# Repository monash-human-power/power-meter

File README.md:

# Cycling power meter final year project <!-- omit in toc -->
Oscar Varney and Jotham Gates, 2024

This is the code repository for a Final Year Project (FYP) to develop a crankset and power meter for Human Powered Vehicles (HPVs).

## Contents <!-- omit in toc -->
- [Getting started](#getting-started)
- [Schematic and PCB layout](#schematic-and-pcb-layout)
- [Code](#code)
  - [Libraries](#libraries)
  - [Tools for updating dates of changed files and versions](#tools-for-updating-dates-of-changed-files-and-versions)
    - [Git Hook for checking dates are correct before committing](#git-hook-for-checking-dates-are-correct-before-committing)
  - [Doxygen documentation](#doxygen-documentation)
- [Scripts and testing](#scripts-and-testing)

## Getting started
- See [here](./documents/getting_started_mqtt.md) for some instructions on getting the power meter to work with MQTT and WiFi.
- See [here](./configs/README.md) for information on configuring the power meter.
- See [here](./documents/mqtt_topics.md) for information on MQTT topics used when communicating using this protocol.
- If you are a member of MHP, then the Notion page for this project can be found [here](https://www.notion.so/monashhumanpower/Power-Pedals-Cranks-FYP-3e6eb409a05642b1ad961b32c2f40aa7).
- The reports submitted for the project are [here](https://github.com/monash-human-power/power-meter-docs/releases) (private repository).

## Schematic and PCB layout
The schematic and PCB layout were completed using [KiCAD 9](https://www.kicad.org/). The design files are in the [`power-meter-pcb`](./power-meter-pcb/) folder.

## Code
The firmware is written to use the Arduino environment of Platform IO and is located in the [`power-meter-code`](power-meter-code) directory.

### Libraries
Install the following libraries, either by using the Arduino library manager or going to their GitHub repository and cloning them.
- [ArduinoJson](https://arduinojson.org/) library for JSON encoding and decoding.
- [ICM42670P](https://github.com/tdk-invn-oss/motion.arduino.ICM42670P) library for communicating with the IMU.
- [BasicLinearAlgebra](https://github.com/tomstewart89/BasicLinearAlgebra/) library for matrix maths. This is also added as a submodule for testing the Kalman filter on a computer.
- [ArduinoBLE](https://github.com/arduino-libraries/ArduinoBLE) library for Bluetooth Low Energy (BLE) communications.
- [PubSubClient](https://pubsubclient.knolleary.net/) library for communicating using MQTT over WiFi.

### Tools for updating dates of changed files and versions
A bash script has been written to update the dates on all modified or staged files (not including untracked files). To perform this operation, run:
```bash
./tools/update_date.sh
```

Another script is included to update the version info on all files and definitions for the code. The files and elements updated include:
- Any `@version` tags in the code directory.
- The `VERSION` definition in [`defines.h`](./power-meter-code/defines.h).
- The Doxygen version number in [`Doxyfile`](./Doxyfile).

As an example:
```bash
./tools/update_version.sh 1.2.3
```

#### Git Hook for checking dates are correct before committing
> This needs to be modified to work with the platform IO structure.
Copy the [`pre-commit`](./tools/pre-commit) file into [`.git/hooks/pre-commit`](.git/hooks/pre-commit). This will check the date of code files and make sure they are up to date.

### Doxygen documentation
Documentation can be automatically generated using Doxygen by running `doxygen` from the root folder of the repository. You might need to install doxygen and graphviz first. The output will be placed in the [`docs`](docs) folder. GitHub actions may be set up later down the track to automatically generate and deploy to GitHub pages on commit- however that would require a public repository and documentation.

To generate a massive appendix for the report, run `./tools/generate_refman.sh`

The output file will be [`refman.pdf`](docs/latex/refman.pdf).

## Scripts and testing
Scripts for testing the board hardware and easing development of certain sections can be found in the [`scripts-testing`](./scripts-testing/) directory. This includes python scripts used to log data over MQTT and plot it.

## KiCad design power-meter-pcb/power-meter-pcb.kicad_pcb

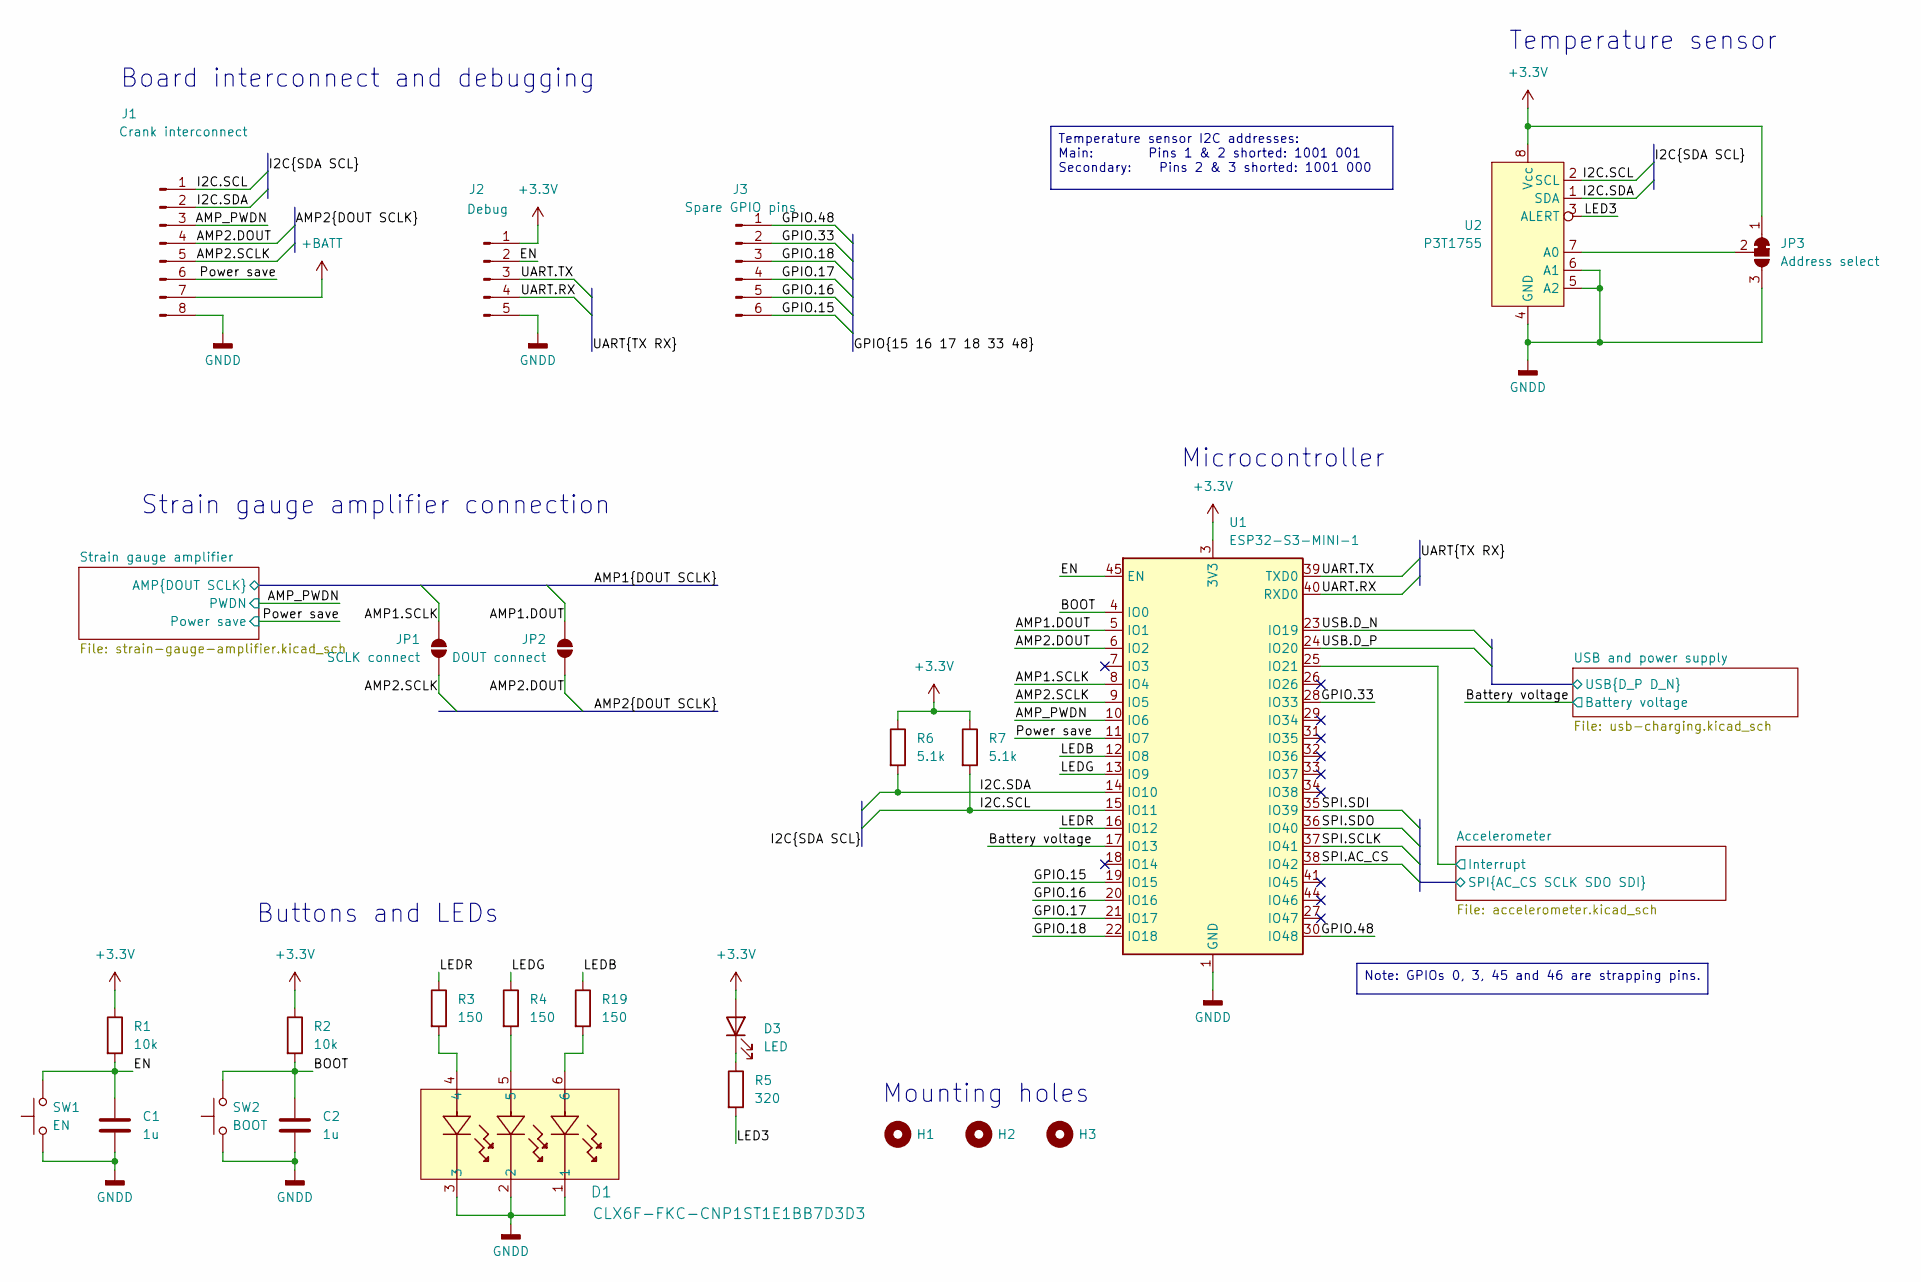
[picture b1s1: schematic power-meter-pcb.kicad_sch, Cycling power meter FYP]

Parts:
C1, C2: 1u; C_0603_1608Metric_Pad1.08x0.95mm_HandSolder
D1: CLX6F-FKC-CNP1ST1E1BB7D3D3; PLCC6_3.4X3.4_CRW-M
D3: LED; LED_0603_1608Metric_Pad1.05x0.95mm_HandSolder
H1, H2, H3: MountingHole; MountingHole_2.2mm_M2
J1: Crank interconnect; JST_PH_S8B-PH-K_1x08_P2.00mm_Horizontal
J2: Debug; PinHeader_1x05_P2.54mm_Vertical
J3: Spare GPIO pins; PinHeader_1x06_P2.00mm_Vertical
JP1: SCLK connect; SolderJumper-2_P1.3mm_Open_RoundedPad1.0x1.5mm
JP2: DOUT connect; SolderJumper-2_P1.3mm_Open_RoundedPad1.0x1.5mm
JP3: Address select; SolderJumper-3_P1.3mm_Open_RoundedPad1.0x1.5mm
R1, R2: 10k; R_0603_1608Metric_Pad0.98x0.95mm_HandSolder
R3, R4, R19: 150; R_0603_1608Metric_Pad0.98x0.95mm_HandSolder
R5: 320; R_0603_1608Metric_Pad0.98x0.95mm_HandSolder
R6, R7: 5.1k; R_0603_1608Metric_Pad0.98x0.95mm_HandSolder
SW1: EN; SW_Push_1P1T_NO_CK_KMR2
SW2: BOOT; SW_Push_1P1T_NO_CK_KMR2
U1: ESP32-S3-MINI-1; ESP32-S2-MINI-1
U2: P3T1755; TSSOP-8_3x3mm_P0.65mm

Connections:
+3.3V: D3.2 (A), J2.1, JP3.1 (A), R1.1, R2.1, R6.1, R7.1, U1.3 (3V3), U2.8 (Vcc); also elsewhere on the board
+BATT: J1.7; also elsewhere on the board
/AMP1.DOUT: JP2.2 (B), U1.5 (IO1); also elsewhere on the board
/AMP1.SCLK: JP1.2 (B), U1.8 (IO4); also elsewhere on the board
/AMP2.DOUT: J1.4, JP2.1 (A), U1.6 (IO2)
/AMP2.SCLK: J1.5, JP1.1 (A), U1.9 (IO5)
/AMP_PWDN: J1.3, U1.10 (IO6); also elsewhere on the board
/Accelerometer/Interrupt: U1.25 (IO21); also elsewhere on the board
/Accelerometer/SPI.AC_CS: U1.38 (IO42); also elsewhere on the board
/Accelerometer/SPI.SCLK: U1.37 (IO41); also elsewhere on the board
/Accelerometer/SPI.SDI: U1.35 (IO39); also elsewhere on the board
/Accelerometer/SPI.SDO: U1.36 (IO40); also elsewhere on the board
/BOOT: C2.2, R2.2, SW2.2, U1.4 (IO0)
/Battery voltage: U1.17 (IO13); also elsewhere on the board
/EN: C1.2, J2.2, R1.2, SW1.2, U1.45 (EN)
/GPIO.15: J3.6, U1.19 (IO15)
/GPIO.16: J3.5, U1.20 (IO16)
/GPIO.17: J3.4, U1.21 (IO17)
/GPIO.18: J3.3, U1.22 (IO18)
/GPIO.33: J3.2, U1.28 (IO33)
/GPIO.48: J3.1, U1.30 (IO48)
/I2C.SCL: J1.1, R7.2, U1.15 (IO11), U2.2 (SCL)
/I2C.SDA: J1.2, R6.2, U1.14 (IO10), U2.1 (SDA)
/LED3: R5.2, U2.3 (ALERT)
/LEDB: R19.1, U1.12 (IO8)
/LEDG: R4.1, U1.13 (IO9)
/LEDR: R3.1, U1.16 (IO12)
/Power save: J1.6, U1.11 (IO7); also elsewhere on the board
/UART.RX: J2.4, U1.40 (RXD0)
/UART.TX: J2.3, U1.39 (TXD0)
/USB and power supply/USB.D_N: U1.23 (IO19); also elsewhere on the board
/USB and power supply/USB.D_P: U1.24 (IO20); also elsewhere on the board
GNDD: C1.1, C2.1, D1.1, D1.2, D1.3, J1.8, J2.5, JP3.3 (B), SW1.1, SW2.1, U1.1 (GND), U1.2 (GND), U1.42 (GND), U1.43 (GND), U1.46 (GND), U1.47 (GND), U1.48 (GND), U1.49 (GND), U1.50 (GND), U1.51 (GND), U1.52 (GND), U1.53 (GND), U1.54 (GND), U1.55 (GND), U1.56 (GND), U1.57 (GND), U1.58 (GND), U1.59 (GND), U1.60 (GND), U1.61 (GND), U1.62 (GND), U1.63 (GND), U1.64 (GND), U1.65 (GND), U2.4 (GND), U2.5 (A2), U2.6 (A1); also elsewhere on the board
unnamed: D1.4, R3.2
unnamed: D1.5, R4.2
unnamed: D1.6, R19.2
unnamed: D3.1 (K), R5.1
unnamed: JP3.2 (C), U2.7 (A0)

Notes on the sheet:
Board interconnect and debugging
Buttons and LEDs
Strain gauge amplifier connection
Microcontroller
Mounting holes
Temperature sensor
Note: GPIOs 0, 3, 45 and 46 are strapping pins.
Temperature sensor I2C addresses: Main: Pins 1 & 2 shorted: 1001 001 Secondary: Pins 2 & 3 shorted: 1001 000

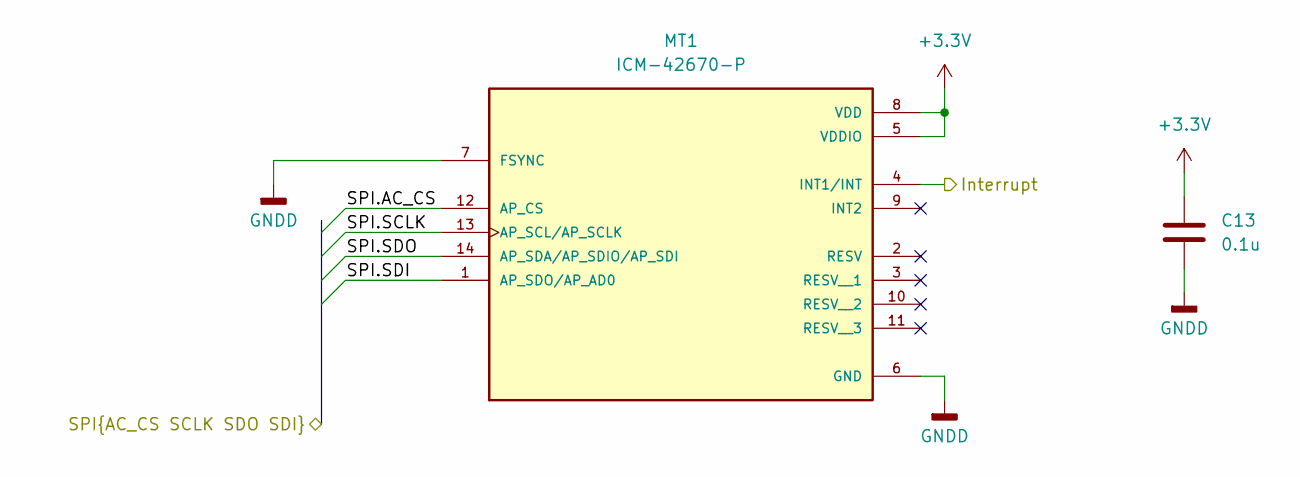
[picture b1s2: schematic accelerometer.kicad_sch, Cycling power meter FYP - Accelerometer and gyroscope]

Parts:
C13: 0.1u; C_0603_1608Metric_Pad1.08x0.95mm_HandSolder
MT1: ICM-42670-P; XDCR_ICM-42670-P; PARTREV 1.1

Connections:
+3.3V: C13.1, MT1.5 (VDDIO), MT1.8 (VDD); also elsewhere on the board
/Accelerometer/Interrupt: MT1.4 (INT1/INT); also elsewhere on the board
/Accelerometer/SPI.AC_CS: MT1.12 (AP_CS); also elsewhere on the board
/Accelerometer/SPI.SCLK: MT1.13 (AP_SCL/AP_SCLK); also elsewhere on the board
/Accelerometer/SPI.SDI: MT1.1 (AP_SDO/AP_AD0); also elsewhere on the board
/Accelerometer/SPI.SDO: MT1.14 (AP_SDA/AP_SDIO/AP_SDI); also elsewhere on the board
GNDD: C13.2, MT1.6 (GND), MT1.7 (FSYNC); also elsewhere on the board

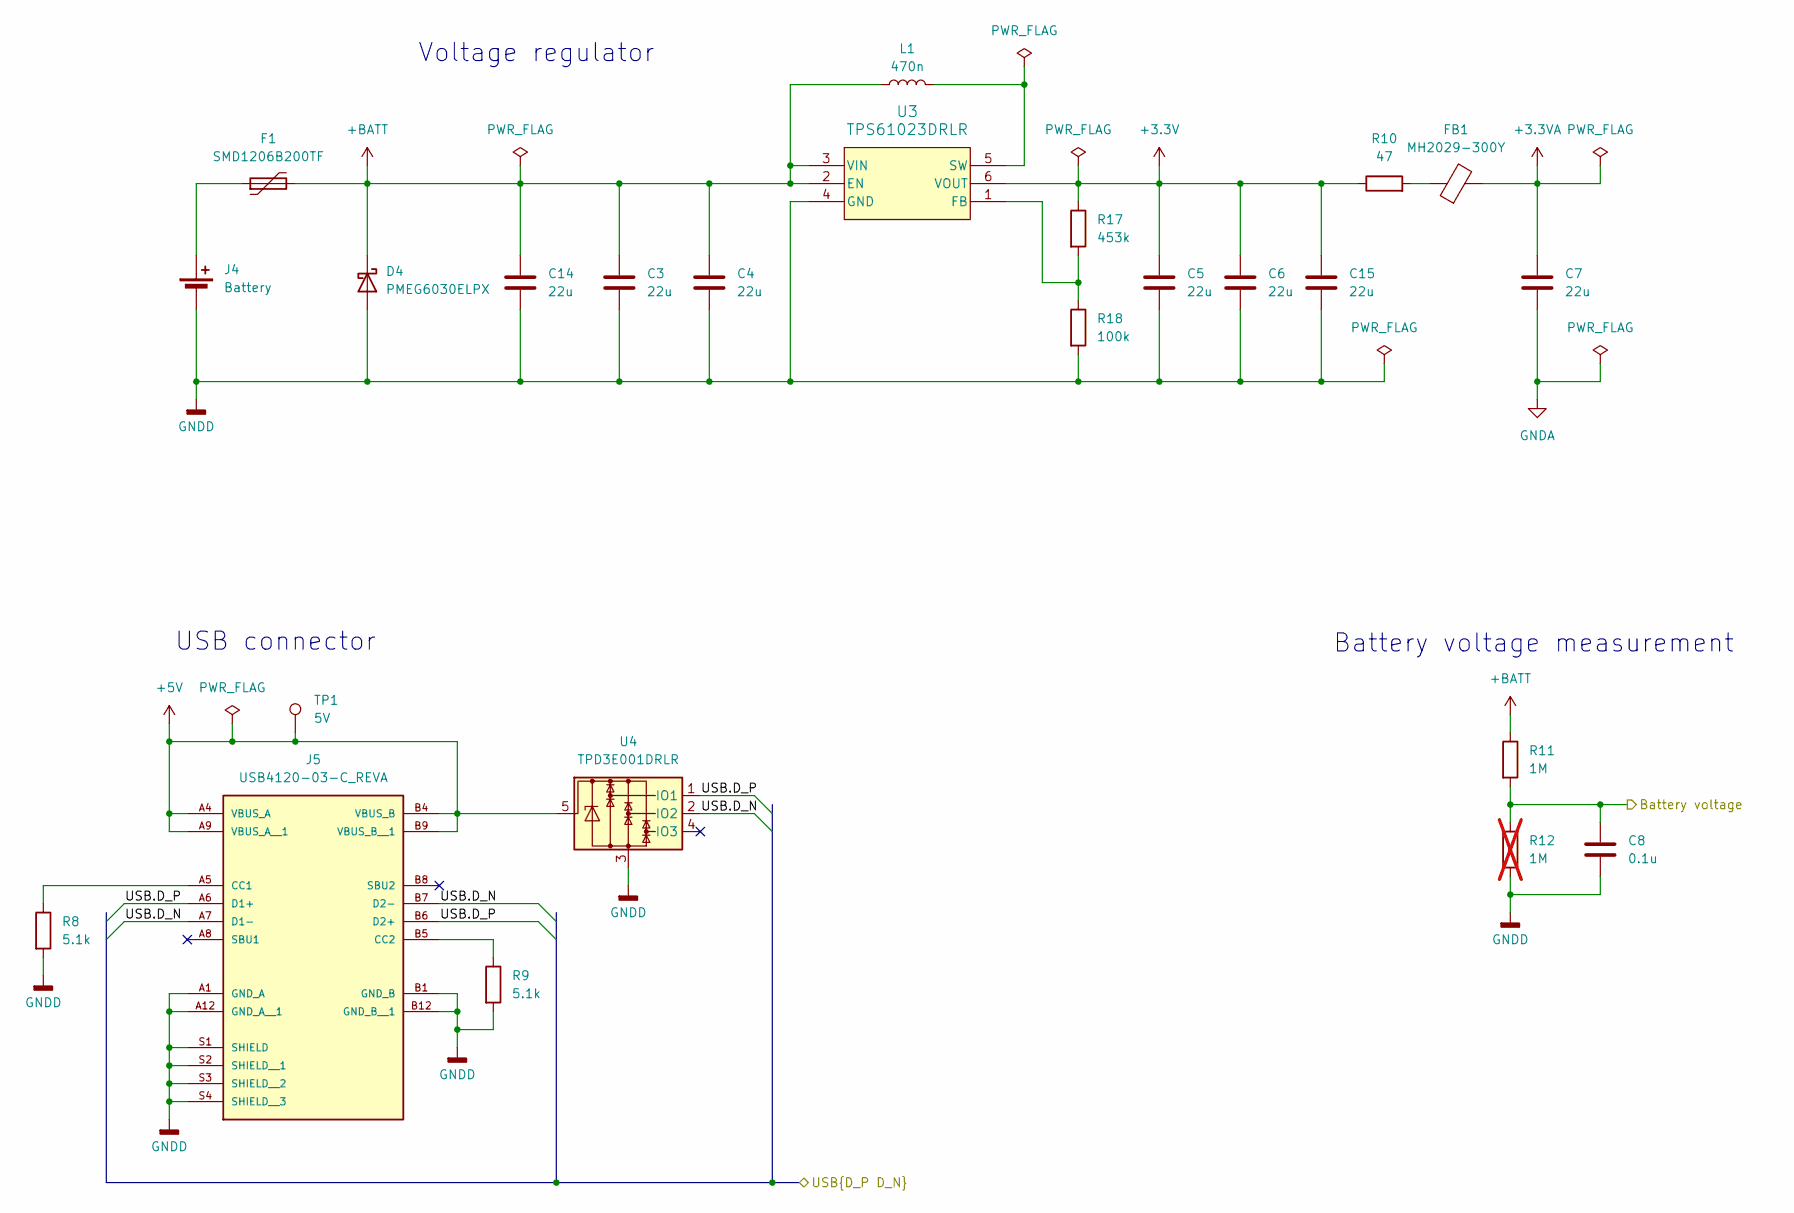
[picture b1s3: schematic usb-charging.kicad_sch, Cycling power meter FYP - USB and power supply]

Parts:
C3, C4, C5, C6, C7, C14, C15: 22u; C_0603_1608Metric_Pad1.08x0.95mm_HandSolder
C8: 0.1u; C_0603_1608Metric_Pad1.08x0.95mm_HandSolder
D4: PMEG6030ELPX; D_SOD-128
F1: SMD1206B200TF; Fuse_1206_3216Metric_Pad1.42x1.75mm_HandSolder
FB1: MH2029-300Y; L_0805_2012Metric
J4: Battery; JST_PH_S2B-PH-K_1x02_P2.00mm_Horizontal
J5: USB4120-03-C_REVA; GCT_USB4120-03-C_REVA; PARTREV A
L1: 470n; L_Vishay_IHLP-1212
R8, R9: 5.1k; R_0603_1608Metric_Pad0.98x0.95mm_HandSolder
R10: 47; R_0603_1608Metric_Pad0.98x0.95mm_HandSolder
R11: 1M; R_0603_1608Metric_Pad0.98x0.95mm_HandSolder
R12: 1M; R_0603_1608Metric_Pad0.98x0.95mm_HandSolder; not fitted
R17: 453k; R_0603_1608Metric_Pad0.98x0.95mm_HandSolder
R18: 100k; R_0603_1608Metric_Pad0.98x0.95mm_HandSolder
TP1: 5V; TestPoint_Pad_1.5x1.5mm
U3: TPS61023DRLR; DRL0006A
U4: TPD3E001DRLR; SOT-553

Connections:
+3.3V: C5.1, C6.1, C15.1, R10.1, R17.1, U3.6 (VOUT); also elsewhere on the board
+3.3VA: C7.1, FB1.2; also elsewhere on the board
+5V: J5.A4 (VBUS_A), J5.A9 (VBUS_A__1), J5.B4 (VBUS_B), J5.B9 (VBUS_B__1), TP1.1, U4.5
+BATT: C3.1, C4.1, C14.1, D4.1 (K), F1.2, L1.1, R11.1, U3.2 (EN), U3.3 (VIN); also elsewhere on the board
/Battery voltage: C8.1, R11.2, R12.1; also elsewhere on the board
/USB and power supply/USB.D_N: J5.A7 (D1-), J5.B7 (D2-), U4.2 (IO2); also elsewhere on the board
/USB and power supply/USB.D_P: J5.A6 (D1+), J5.B6 (D2+), U4.1 (IO1); also elsewhere on the board
GNDA: C7.2; also elsewhere on the board
GNDD: C3.2, C4.2, C5.2, C6.2, C8.2, C14.2, C15.2, D4.2 (A), J4.2 (-), J5.A1 (GND_A), J5.A12 (GND_A__1), J5.B1 (GND_B), J5.B12 (GND_B__1), J5.S1 (SHIELD), J5.S2 (SHIELD__1), J5.S3 (SHIELD__2), J5.S4 (SHIELD__3), R8.2, R9.2, R12.2, R18.2, U3.4 (GND), U4.3; also elsewhere on the board
unnamed: FB1.1, R10.2
unnamed: F1.1, J4.1 (+)
unnamed: J5.A5 (CC1), R8.1
unnamed: J5.B5 (CC2), R9.1
unnamed: R17.2, R18.1, U3.1 (FB)
unnamed: L1.2, U3.5 (SW)

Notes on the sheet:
Battery voltage measurement
USB connector
Voltage regulator

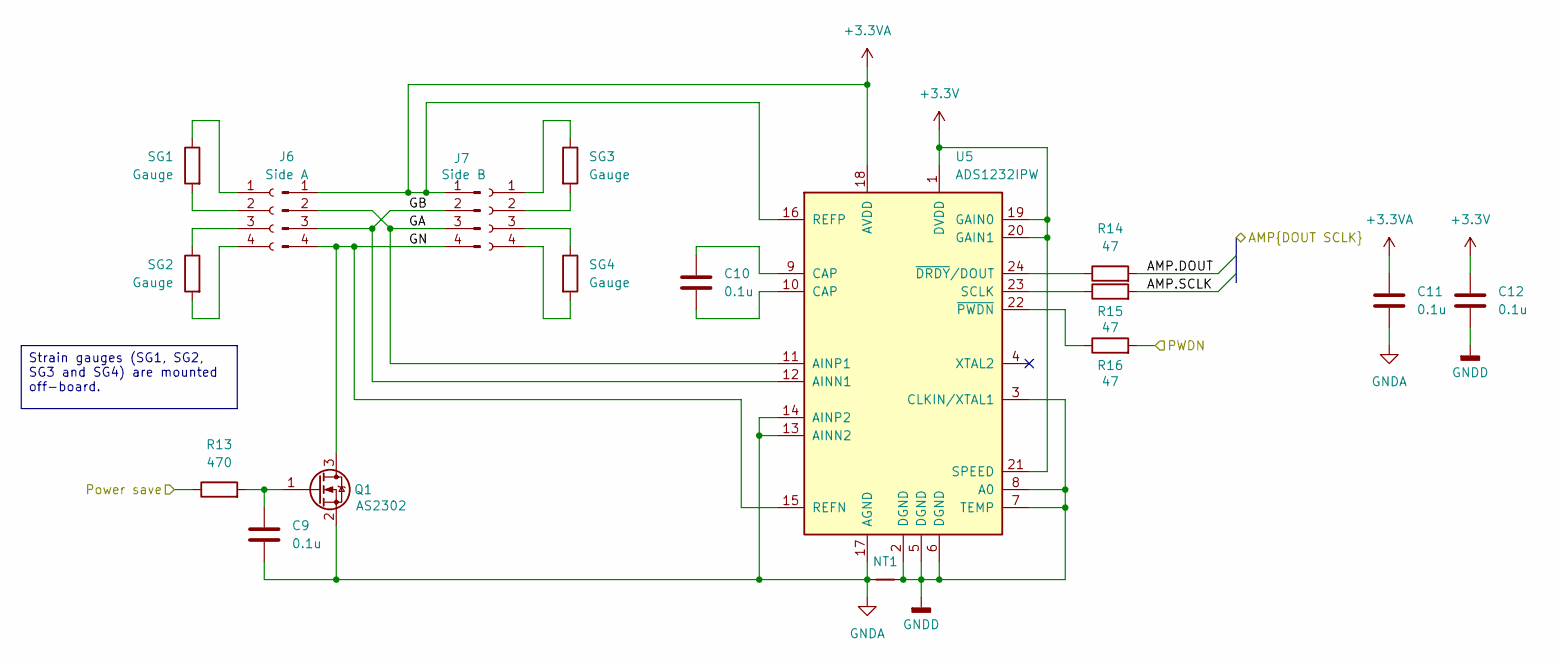
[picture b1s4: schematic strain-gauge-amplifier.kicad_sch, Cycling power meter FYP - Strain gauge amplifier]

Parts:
C9, C10, C11, C12: 0.1u; C_0603_1608Metric_Pad1.08x0.95mm_HandSolder
J6: Side A; PinHeader_1x04_P2.54mm_Vertical
J7: Side B; PinHeader_1x04_P2.54mm_Vertical
NT1: NetTie_2; NetTie-2_SMD_Pad0.5mm
Q1: AS2302; TSOT-23
R13: 470; R_0603_1608Metric_Pad0.98x0.95mm_HandSolder
R14, R15, R16: 47; R_0603_1608Metric_Pad0.98x0.95mm_HandSolder
SG1, SG2, SG3, SG4: Gauge
U5: ADS1232IPW; TSSOP-24_4.4x7.8mm_P0.65mm

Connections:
+3.3V: C12.1, U5.1 (DVDD), U5.19 (GAIN0), U5.20 (GAIN1), U5.21 (SPEED); also elsewhere on the board
+3.3VA: C11.1, J6.1, J7.1, U5.16 (REFP), U5.18 (AVDD); also elsewhere on the board
/AMP1.DOUT: R14.2; also elsewhere on the board
/AMP1.SCLK: R15.2; also elsewhere on the board
/AMP_PWDN: R16.2; also elsewhere on the board
/Power save: R13.1; also elsewhere on the board
/Strain gauge amplifier/GA: J6.2, J7.3, U5.11 (AINP1)
/Strain gauge amplifier/GB: J6.3, J7.2, U5.12 (AINN1)
/Strain gauge amplifier/GN: J6.4, J7.4, Q1.3 (D), U5.15 (REFN)
GNDA: C9.2, C11.2, NT1.1, Q1.2 (S), U5.13 (AINN2), U5.14 (AINP2), U5.17 (AGND); also elsewhere on the board
GNDD: C12.2, NT1.2, U5.2 (DGND), U5.3 (CLKIN/XTAL1), U5.5 (DGND), U5.6 (DGND), U5.7 (TEMP), U5.8 (A0); also elsewhere on the board
unnamed: C10.1, U5.9 (CAP)
unnamed: C10.2, U5.10 (CAP)
unnamed: C9.1, Q1.1 (G), R13.2
unnamed: SG1.1, SG1.2, SG2.1, SG2.2, SG3.1, SG3.2, SG4.1, SG4.2
unnamed: R15.1, U5.23 (SCLK)
unnamed: R14.1, U5.24 (~DRDY/DOUT)
unnamed: R16.1, U5.22 (~PWDN)

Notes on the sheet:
Strain gauges (SG1, SG2, SG3 and SG4) are mounted off-board.

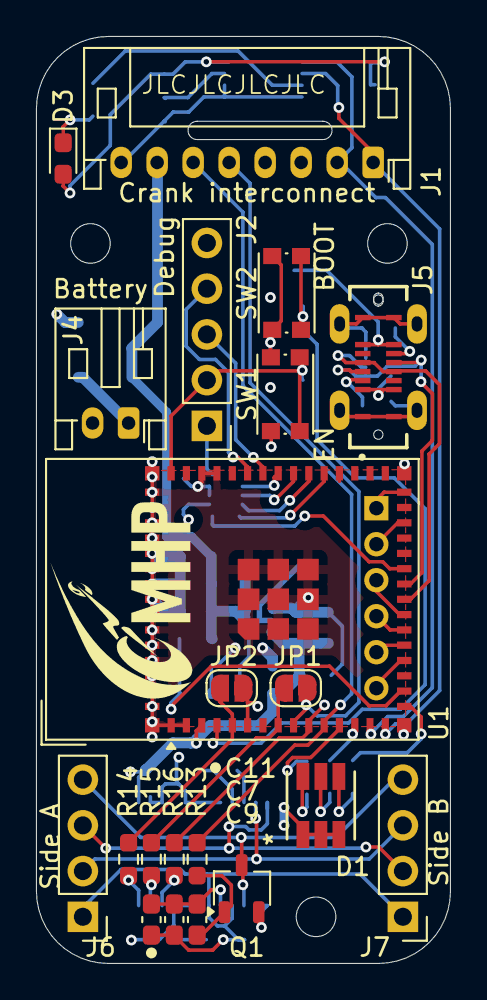
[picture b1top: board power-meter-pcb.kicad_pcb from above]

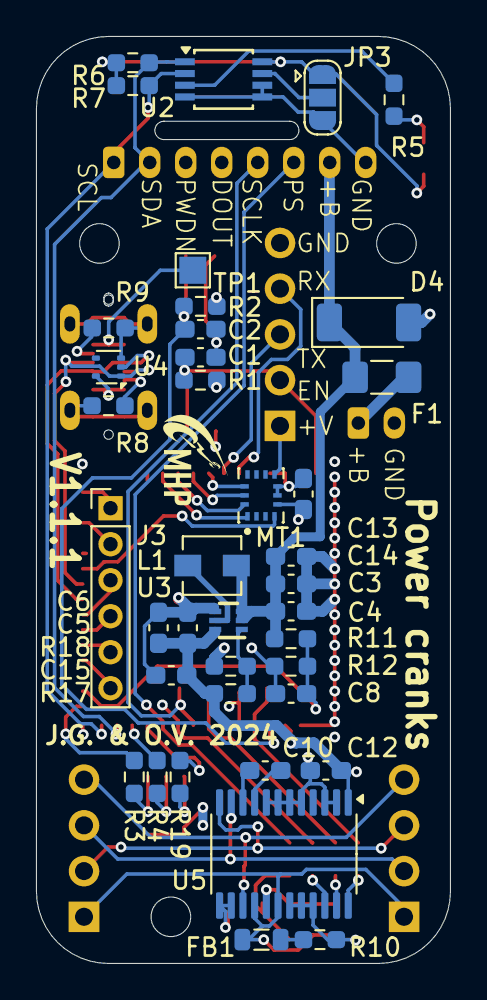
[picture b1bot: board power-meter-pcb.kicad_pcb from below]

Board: 4 copper layers, 23.0 x 51.5 mm, 64 parts (40 on the bottom side), 56 nets.

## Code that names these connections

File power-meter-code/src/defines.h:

/**
 * @file defines.h
 * @brief Useful pin and constant definitions and preprocessor directives.
 *
 *
 * @author Jotham Gates and Oscar Varney, MHP
 * @version 0.1.0
 * @date 2025-08-16
 */
#pragma once
#define SW_VERSION "s0.1.0"
#include "constants.h"

/**
 * Hardware versions
 */
// Check the versions are valid.
#if !defined(HW_VERSION)
#error "No hardware version specified (set this in constants.h)."
#endif
#if (HW_VERSION != HW_VERSION_V1_0_4) && (HW_VERSION != HW_VERSION_V1_0_5) && (HW_VERSION != HW_VERSION_V1_1_1)
#error "Unsupported hardware version specified (set this in constants.h)"
#endif

// Define a nicely formatted version string according to the version.
#if HW_VERSION == HW_VERSION_V1_0_4
#define HW_VERSION_STR "v1.0.4"
#elif HW_VERSION == HW_VERSION_V1_0_5
#define HW_VERSION_STR "v1.0.5"
#elif HW_VERSION == HW_VERSION_V1_1_1
#define HW_VERSION_STR "v1.1.1"
#endif

/**
 * Pins and hardware details
 */
// Strain gauge amplifiers
#define PIN_AMP1_DOUT 1
#define PIN_AMP1_SCLK 4
#define PIN_AMP2_DOUT 2
#define PIN_AMP2_SCLK 5
#define PIN_AMP_PWDN 6
#define PIN_POWER_SAVE 7
#define AMP_BIT_DEPTH 24

// Buttons and LEDs
#if (HW_VERSION == HW_VERSION_V1_0_4) || (HW_VERSION == HW_VERSION_V1_0_5)
#define PIN_LEDR 8
#define PIN_LEDG 9
// #define PIN_LEDB 12 // No Blue LED
#define PIN_CONNECTION_LED PIN_LEDG
#elif HW_VERSION == HW_VERSION_V1_1_1
#define PIN_LEDR 12
#define PIN_LEDG 9
#define PIN_LEDB 8
#define PIN_CONNECTION_LED PIN_LEDG
#define HAS_BLUE_LED
#endif

#define PIN_BOOT 0

// I2C for temperature sensor
#define PIN_I2C_SDA 10
#define PIN_I2C_SCL 11
#define I2C_BUS_FREQ 400000
#define TEMP1_I2C 0b1001001
#define TEMP2_I2C 0b1001000

// Accelerometer
#if (HW_VERSION == HW_VERSION_V1_0_4) || (HW_VERSION == HW_VERSION_V1_0_5)
#define PIN_ACCEL_INTERRUPT 38
#elif (HW_VERSION == HW_VERSION_V1_1_1)
#define ACCEL_RTC_CAPABLE
#define PIN_ACCEL_INTERRUPT 21
#endif
#define PIN_SPI_SDI 39
#define PIN_SPI_SDO 40
#define PIN_SPI_SCLK 41
#define PIN_SPI_AC_CS 42
#define IMU_SAMPLE_RATE 100 // Options are 12, 25, 50, 100, 200, 400, 800, 1600 Hz (any other value defaults to 100 Hz).
#define IMU_ACCEL_RANGE 4   // Options are 2, 4, 8, 16 G (any other value defaults to 16 G).
#define IMU_GYRO_RANGE 2000 // Options are 250, 500, 1000, 2000 dps (any other value defaults to 2000 dps).

// Power management
#if HW_VERSION == HW_VERSION_V1_0_4
#define PIN_BATTERY_VOLTAGE 12 // As per design.
#elif HW_VERSION == HW_VERSION_V1_0_5
#define PIN_BATTERY_VOLTAGE 15 // Bodge wire as original is shorted to ground.
#elif HW_VERSION == HW_VERSION_V1_1_1
#define PIN_BATTERY_VOLTAGE 13
#endif

// Extra GPIO pins
#if (HW_VERSION == HW_VERSION_V1_0_4) || (HW_VERSION == HW_VERSION_V1_0_5)
// Spare GPIO pins are // TODO:
#define SPARE_GPIO_6 15
#elif (HW_VERSION == HW_VERSION_V1_1_1)
#define SPARE_GPIO_1 48
#define SPARE_GPIO_2 33
#define SPARE_GPIO_3 18
#define SPARE_GPIO_4 17
#define SPARE_GPIO_5 16
#define SPARE_GPIO_6 15
#endif

#define PIN_LEDS 43

// Communications
#define PIN_UART_TX0
#define PIN_UART_RX0
#define SERIAL_BAUD 115200
#define PIN_USB_DN 19
#define PIN_USB_DP 20

/**
 * Logging
 * // TODO: Make work over USB.
 */
// Logging (with mutexes)
#define SERIAL_TAKE() xSemaphoreTake(serialMutex, portMAX_DELAY)
#define SERIAL_GIVE() xSemaphoreGive(serialMutex)
#define LOGV(tag, format, ...)                 \
    SERIAL_TAKE();                             \
    log_v("[%s] " format, tag, ##__VA_ARGS__); \
    SERIAL_GIVE()
#define LOGD(tag, format, ...)                 \
    SERIAL_TAKE();                             \
    log_d("[%s] " format, tag, ##__VA_ARGS__); \
    SERIAL_GIVE()
#define LOGI(tag, format, ...)                 \
    SERIAL_TAKE();                             \
    log_i("[%s] " format, tag, ##__VA_ARGS__); \
    SERIAL_GIVE()
#define LOGW(tag, format, ...)                 \
    SERIAL_TAKE();                             \
    log_w("[%s] " format, tag, ##__VA_ARGS__); \
    SERIAL_GIVE()
#define LOGE(tag, format, ...)                 \
    SERIAL_TAKE();                             \
    log_e("[%s] " format, tag, ##__VA_ARGS__); \
    SERIAL_GIVE()

// https://gcc.gnu.org/onlinedocs/gcc-4.8.5/cpp/Stringification.html
#define xstringify(s) stringify(s)
#define stringify(s) #s

/**
 * @brief Enumerator to represent each side of the power meter.
 *
 */
enum EnumSide
{
    SIDE_LEFT = 0,
    SIDE_RIGHT = 1,
    SIDE_IMU_TEMP = 2
};

/**
 * @brief Enumerator to represent the selected connection method.
 *
 */
enum EnumConnection
{
    CONNECTION_MQTT,
    CONNECTION_BLE
};

/**
 * @brief Enumerator for connection state
 *
 */
enum EnumConnState
{
    CONN_STATE_DISABLED,
    CONN_STATE_CONNECTING_1,
    CONN_STATE_CONNECTING_2,
    CONN_STATE_ACTIVE,
    CONN_STATE_SHUTTING_DOWN,
    CONN_STATE_SENDING,
    CONN_STATE_RECEIVING
};

/**
 * WiFi settings.
 */
#define MQTT_TOPIC_SEPARATOR '/'
#define RECONNECT_DELAY 1000
#define MQTT_RETRY_ITERATIONS 20
#define WIFI_RECONNECT_ATTEMPT_TIME 60000 // If not connected in 1 minute, disconnect and attempt again.

// Constant constants.
#define GRAVITY 9.81                   // Accelerometer operates in g, calculations are done in SI units.
#define KALMAN_X0 {0, 0}               // Initial state.
#define KALMAN_P0 {1e6, 1e6, 1e6, 1e6} // Initial covariance. High numbers mean we don't know to start with.

#define SUPPLY_VOLTAGE 3300             // Power supply in mV, used to calculate the battery voltage.
#define VOLTAGE_DIVIDER_RATIO 2         // Set to 1 if PIN_BATTERY_VOLTAGE is directly connected to the battery (the original V1.0.4 and first V1.1.1 boards are currently like this).
#define OFFSET_COMPENSATION_SAMPLES 200 // How many samples to average to calculate the offset.
#define INVALID_TEMPERATURE -1000       // Invalid temperature so that I don't have to work out formatting NaN in a JSON compatible way.

// Settings for ArduinoJSON
#define ARDUINOJSON_NEGATIVE_EXPONENTIATION_THRESHOLD 1e-2
#define ARDUINOJSON_POSITIVE_EXPONENTIATION_THRESHOLD 1e4
#include "Arduino.h"

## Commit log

2024-04-17 Created KiCAD project
2024-04-17 Filling out the readme file
2024-04-18 Added amplifier, IMU, inter board connections
2024-04-18 Assigning footprints, extremely rough idea of size
2024-04-20 Added power supply to PCB
2024-04-20 Started PCB layout
2024-04-22 Adding filtering and pullup resistors, board layout
2024-04-23 Routing and component placement continues
2024-04-23 Tidying schematic
2024-05-01 Improved board outline, in the middle of layout changes
2024-05-02 Layout almost done, but will likely swap to a 4 layer PCB
2024-05-09 Board layout about done, front silkscreen ok
2024-05-14 Cleaning up PCB back and title box
2024-05-24 Exporting BOM, added layer to board sheet
2024-06-14 Smaller PCB design started
2024-06-14 Smaller board layout planned
2024-06-16 More track routing
2024-06-21 Board mostly routed, schematic page layout cleaned up
2024-06-23 Silkscreen done
2024-06-23 Started code
2024-06-24 Added date updating script.
2024-06-25 Added doxygen file, updated versioning scripts, add pin definitions and states, updated readme
2024-06-25 Added error message to update date
2024-06-26 Moved to subfolders, started connection class.
2024-06-28 Started strain gauge and temp sensors classes
2024-06-28 Added date checking git hook
2024-07-03 Added Kalman filter and testing for it
2024-07-04 Started IMU manager to connect kalman filter
2024-07-05 Re-centred schematics, added header for spare GPIO pins, touched up logos
2024-07-09 Moved IMU class to its own file, kalman filter should be updated automatically
2024-07-09 Edited doxyfile to show private attributes
2024-07-11 Added LED driven by temp sensor, updated numbering
2024-07-12 Fixed LED3 wiring
2024-07-15 Cap on ADC DC pin moved to next to pin
2024-07-18 Filled out connection base classes
2024-07-19 Adding states to connection state machine
2024-07-21 MQTT Connection should be mostly implemented
2024-07-22 Compiles, state name pointer doesn't work
2024-07-26 Testing scripts work
2024-07-29 Compiles with ESP32 board version 2.011, needs features from board version 3+
2024-07-31 Successfully sleeps, wakes, connects to wifi and mqtt and publishes
2024-07-31 Amost runs on actual hardware
2024-08-01 Sends regular MQTT messages with IMUData
2024-08-02 Added python IMU logger, fixed scaled units for IMU,modified IMUData to have some raw data.
2024-08-04 Added OTA Updates
2024-08-04 Edited connections base class to be single parent, fixed kalman spinslock
2024-08-07 Started adding config
2024-08-07 Can get and set configs over MQTT
2024-08-08 Reads temperature, flashes amber LED, corrected bus labelling error in schematic.
2024-08-08 Fixing I2C track labelling. V1.1.0
2024-08-09 Fixed SPI pin labels
2024-08-10 Kalman filter appears to work
2024-08-10 Rotations are counted
2024-08-14 Started writing code to read from strai ngauges, moved temperatures to their own file (untested)
2024-08-16 Kalman filter works still, swapped to USB OTG, can enter DFU using software.
2024-08-17 Live graph of position and speed works
2024-08-18 Added GPIO testing script
2024-08-20 Adding plot_imu to plot saved data over time
2024-08-21 Added testing script for all LEDs and temperature sensors.
2024-08-22 Reading from ADC works
2024-08-23 Adding namespaces for BLE characteristics
2024-08-23 Low data rate messages sent, can swap between connections, issues with data rates possibly
2024-08-23 Removed logging for each MQTT message to fix performance, moved keeping track of interrupt timings to the isr. Not tested for the ADC ISR templates.
2024-08-24 Cadence works over BLE
2024-08-30 Python scripts to log and plot strain data saved.
2024-09-01 Added config fot strain gauges, CLI to get and set config
2024-09-03 Torque and average power are calculated and handled, CLI improved, offset compensation enabled.
2024-09-04 Swapped to platform IO
2024-09-04 Sends all IMU data, runs out of RAM
2024-09-07 USB CLI works again, buffer size issues with IMU data fixed, memory usage logged
2024-09-08 Uses a TPS61022 Voltage regulator - will change for easier soldering
2024-09-08 New voltage regulator layout about done
2024-09-09 Added buffer size to conf, flashes an LED on TX, logger saves power and fully converts housekeeping to csv
2024-09-09 PCB modifications about done
2024-09-10 Added slot for thermal isolation
2024-09-10 Sorting out parts to order and component changes
2024-09-10 Added 3D model for RGB LED
2024-09-10 Fixed USB data pin polarity in one orientation, added test point
2024-09-20 First attempt at new hardware version
2024-09-22 Rev 1.1.1 works, LED task basics work
2024-09-24 Plot strain gauges shows ADC raw and min and max
2024-09-25 Multiple live graphs are displayed
2024-09-26 Swapped calibration to Nm
2024-09-27 Added offsets to housekeeping, option to use provided torque in plot strain
2024-09-27 Power is no longer off by 1e6, slow data is correctly sent to csv and graph, help strings updated.
2024-09-27 Plots cadence and power over time, flipped left and right order over on strain graph for aesthetics
2024-09-28 Swapped to arduinojson to serialise configs, changed config format, added mqtt and wifi to conf, now uses platformio libraries instead of arduino library folder.
2024-09-28 Sleep mode implemented (tested on v1.0.4, not v1.1.1)
2024-09-30 Added MQTT topics page, added flat battery shutdown,
2024-10-01 Added 0 to cadence when not rotating.
2024-10-02 Added usage documentation
2024-10-02 Added FIT file support to plotter, time offsets, plotting individual left and right power, corrected power balance flipped.
2024-10-02 Limiting times show in plot cadence power
2024-10-04 Added temperature plot, strain and imu now correct for device time being reset.
2024-10-04 Moved logging parts to common, can now plot historical polar data,
2024-10-05 Added the ability to scale a training tracker (rally) data
2024-10-07 Started script to add calibration data
2024-10-11 Removed unnecessary call to turn off red LED, simplified calibration graphs
2024-10-11 Changed calibration title
2024-10-14 Generating graphs for poster and video, updating readme (may wish to rever changes to graphs)
2024-10-17 Added ability to export power comparisons to CSV
2024-10-23 IMU graph as submitted in final report
2024-10-23 Calibration can export JSON, recalculate script started
2024-10-25 Added is transmitting to strain data.
2024-10-26 Logs whether currently transmitting
2025-01-31 Started recalculating script, fixed power reporting for BLE
2025-01-31 Added hardware version to the platform file
2025-08-16 Updated to KiCAD 9.0, copied parameters into constants.example.h, doubled reported battery voltage to suit latest boards with voltage divider fitted.
2025-12-14 Basic patterns working.
2025-12-16 Good enough
2025-12-19 Scaling some lights based on speed.
